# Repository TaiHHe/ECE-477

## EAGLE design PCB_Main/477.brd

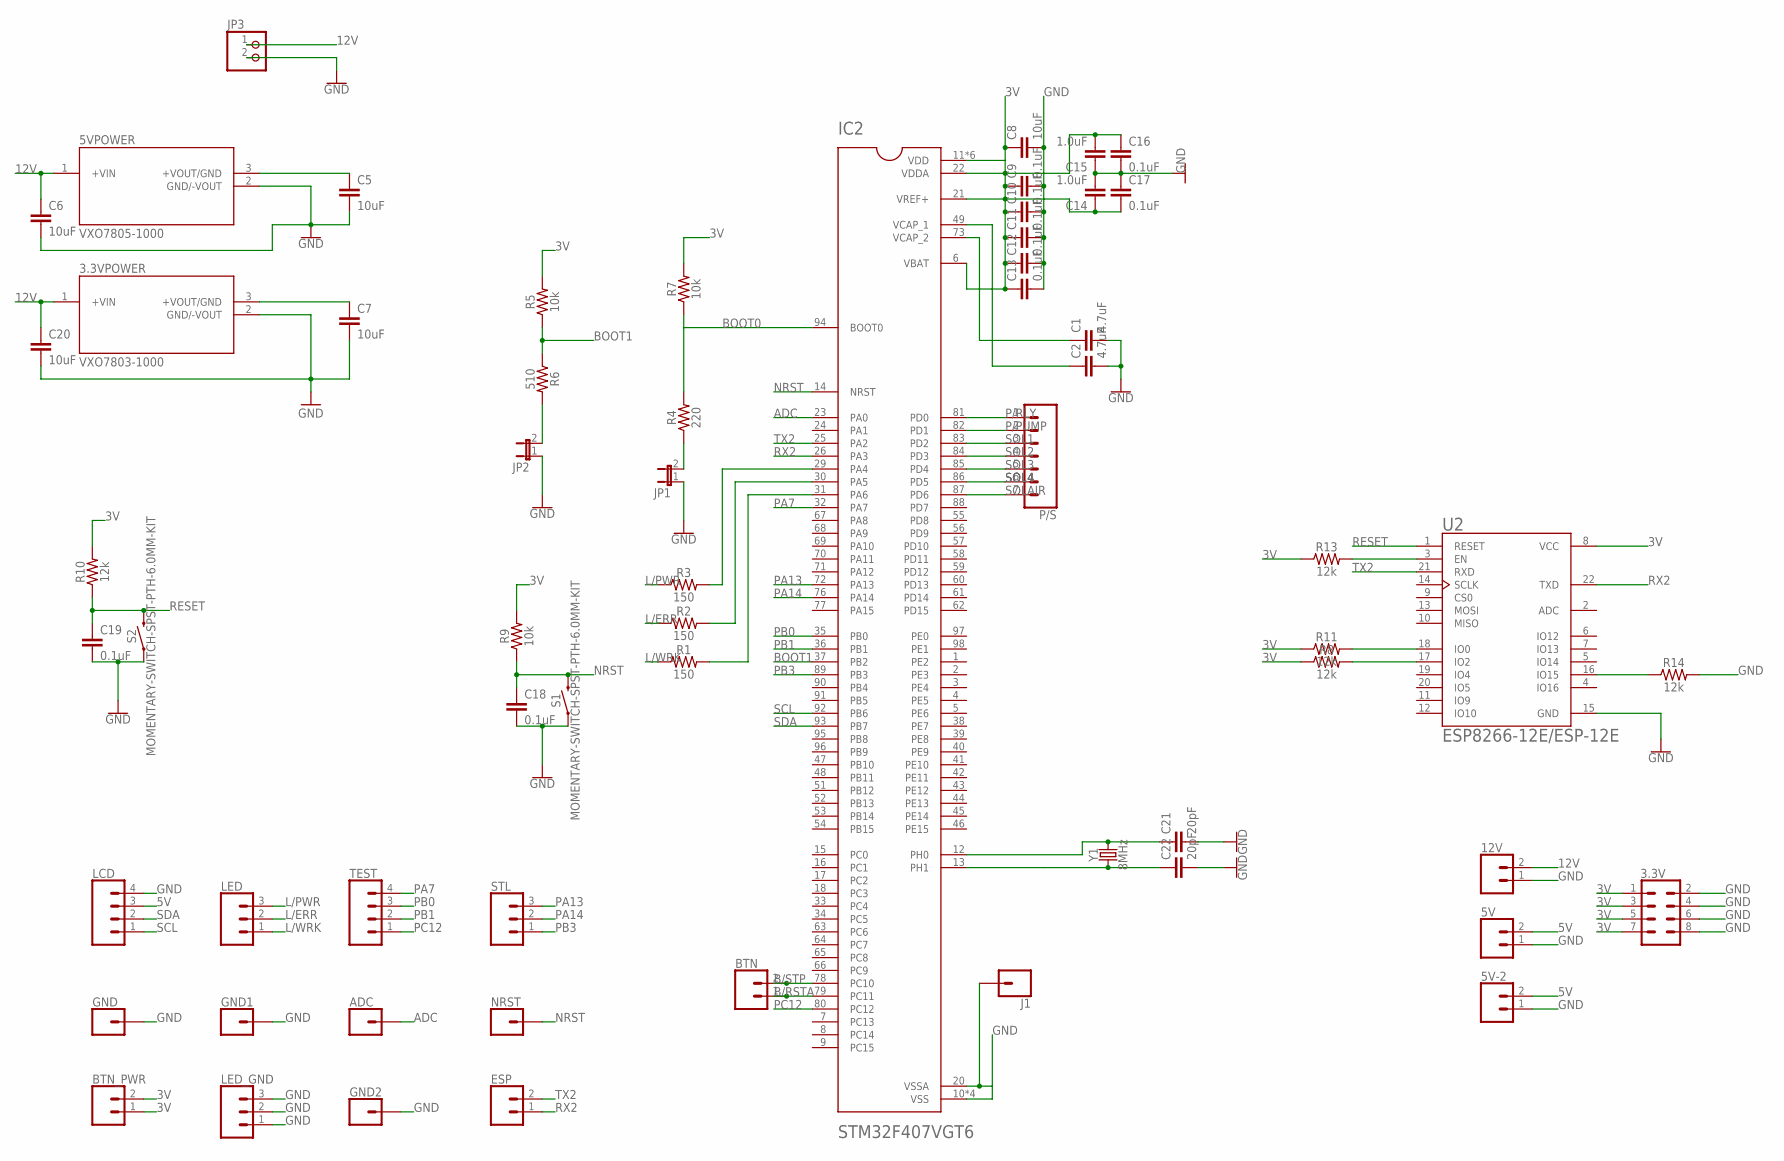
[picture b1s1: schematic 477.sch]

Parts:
3.3V: CONN_04X2; 2X4
3.3VPOWER: VXO7803-1000; CONV_VXO7803-1000
5V, 5V-2, 12V: CONN_02; 1X02
5VPOWER: VXO7805-1000; CONV_VXO7805-1000
ADC: CONN_01; 1X01
BTN: CONN_02; 1X02
BTN_PWR: CONN_02; 1X02
C1, C2: 4.7uF; 0603
C5, C6, C7, C8, C20: 10uF; 0603
C9, C10, C11, C12, C13, C16, C17, C18, C19: 0.1uF; 0402
C14, C15: 1.0uF; 0402
C21, C22: 20pF; 0603
ESP: CONN_02; 1X02
GND, GND1: CONN_01PTH_NO_SILK_YES_STOP; 1X01_NO_SILK
GND2: CONN_01; 1X01
IC2: STM32F407VGT6; QFP50P1600X1600X160-100N
J1: CONN_01PTH_NO_SILK_YES_STOP; 1X01_NO_SILK
JP1, JP2: JP1E; JP1
JP3: PINHD-1X2; 1X02
LCD: CONN_04; 1X04
LED: CONN_03; 1X03
LED_GND: CONN_03; 1X03
NRST: CONN_01; 1X01
P/S: CONN_07; 1X07
R1, R2, R3: 150; 0603
R4: 220; 0603
R5, R7, R9: 10k; 0603
R6: 510; 0603
R8, R10, R11, R13, R14: 12k; 0603
S1, S2: MOMENTARY-SWITCH-SPST-PTH-6.0MM-KIT; TACTILE_SWITCH_PTH_6.0MM_KIT
STL: CONN_03; 1X03
TEST: CONN_04; 1X04
U2: ESP8266-12E/ESP-12E; XCVR_ESP8266-12E/ESP-12E
Y1: 8MHz; HC49UP

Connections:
3V: 3.3V.1, 3.3V.3, 3.3V.5, 3.3V.7, 3.3VPOWER.3 (+VOUT/GND), BTN_PWR.1, BTN_PWR.2, C7.1, C8.1, C9.1, C10.1, C11.1, C12.1, C13.1, C14.1, C15.2, C16.1, C17.2, IC2.6 (VBAT), IC2.11 (VDD), IC2.19 (VDD), IC2.21 (VREF+), IC2.22 (VDDA), IC2.28 (VDD), IC2.50 (VDD), IC2.75 (VDD), IC2.100 (VDD), R5.2, R7.2, R8.1, R9.2, R10.2, R11.1, R13.1, U2.8 (VCC)
5V: 5V.2, 5V-2.2, 5VPOWER.3 (+VOUT/GND), C5.1, LCD.3
12V: 3.3VPOWER.1 (+VIN), 5VPOWER.1 (+VIN), 12V.2, C6.1, C20.1, JP3.1
ADC: ADC.1, IC2.23 (PA0)
B/RSTA: BTN.1, IC2.79 (PC11)
B/STP: BTN.2, IC2.78 (PC10)
BOOT0: IC2.94 (BOOT0), R4.2, R7.1
BOOT1: IC2.37 (PB2), R5.1, R6.1
EN: R13.2, U2.3 (EN)
GND: 3.3V.2, 3.3V.4, 3.3V.6, 3.3V.8, 3.3VPOWER.2 (GND/-VOUT), 5V.1, 5V-2.1, 5VPOWER.2 (GND/-VOUT), 12V.1, C1.2, C2.2, C5.2, C6.2, C7.2, C8.2, C9.2, C10.2, C11.2, C12.2, C13.2, C14.2, C15.1, C16.2, C17.1, C18.2, C19.2, C20.2, C21.2, C22.2, GND.1, GND1.1, GND2.1, IC2.10 (VSS), IC2.27 (VSS), IC2.74 (VSS), IC2.99 (VSS), JP1.1, JP2.1, JP3.2, LCD.4, LED_GND.1, LED_GND.2, LED_GND.3, R14.2, S1.1, S2.1, U2.15 (GND)
L/ERR: LED.2, R2.1
L/PWR: LED.3, R3.1
L/WRK: LED.1, R1.1
unnamed: IC2.29 (PA4), R3.2
unnamed: IC2.30 (PA5), R2.2
unnamed: C22.1, IC2.13 (PH1), Y1.1
unnamed: IC2.31 (PA6), R1.2
unnamed: R11.2, U2.18 (IO0)
unnamed: R8.2, U2.17 (IO2)
unnamed: R14.1, U2.16 (IO15)
unnamed: C21.1, IC2.12 (PH0), Y1.2
unnamed: C1.1, IC2.73 (VCAP_2)
unnamed: JP2.2, R6.2
unnamed: C2.1, IC2.49 (VCAP_1)
unnamed: IC2.20 (VSSA), J1.1
unnamed: JP1.2, R4.1
NRST: C18.1, IC2.14 (NRST), NRST.1, R9.1, S1.3 (2)
P/PUMP: IC2.82 (PD1), P/S.2
P/RLY: IC2.81 (PD0), P/S.1
PA7: IC2.32 (PA7), TEST.4
PA13: IC2.72 (PA13), STL.3
PA14: IC2.76 (PA14), STL.2
PB0: IC2.35 (PB0), TEST.3
PB1: IC2.36 (PB1), TEST.2
PB3: IC2.89 (PB3), STL.1
PC12: IC2.80 (PC12), TEST.1
RESET: C19.1, R10.1, S2.3 (2), U2.1 (RESET)
RX2: ESP.1, IC2.26 (PA3), U2.22 (TXD)
SCL: IC2.92 (PB6), LCD.1
SDA: IC2.93 (PB7), LCD.2
SOL1: IC2.83 (PD2), P/S.3
SOL2: IC2.84 (PD3), P/S.4
SOL3: IC2.85 (PD4), P/S.5
SOL4: IC2.86 (PD5), P/S.6
SOLAIR: IC2.87 (PD6), P/S.7
TX2: ESP.2, IC2.25 (PA2), U2.21 (RXD)

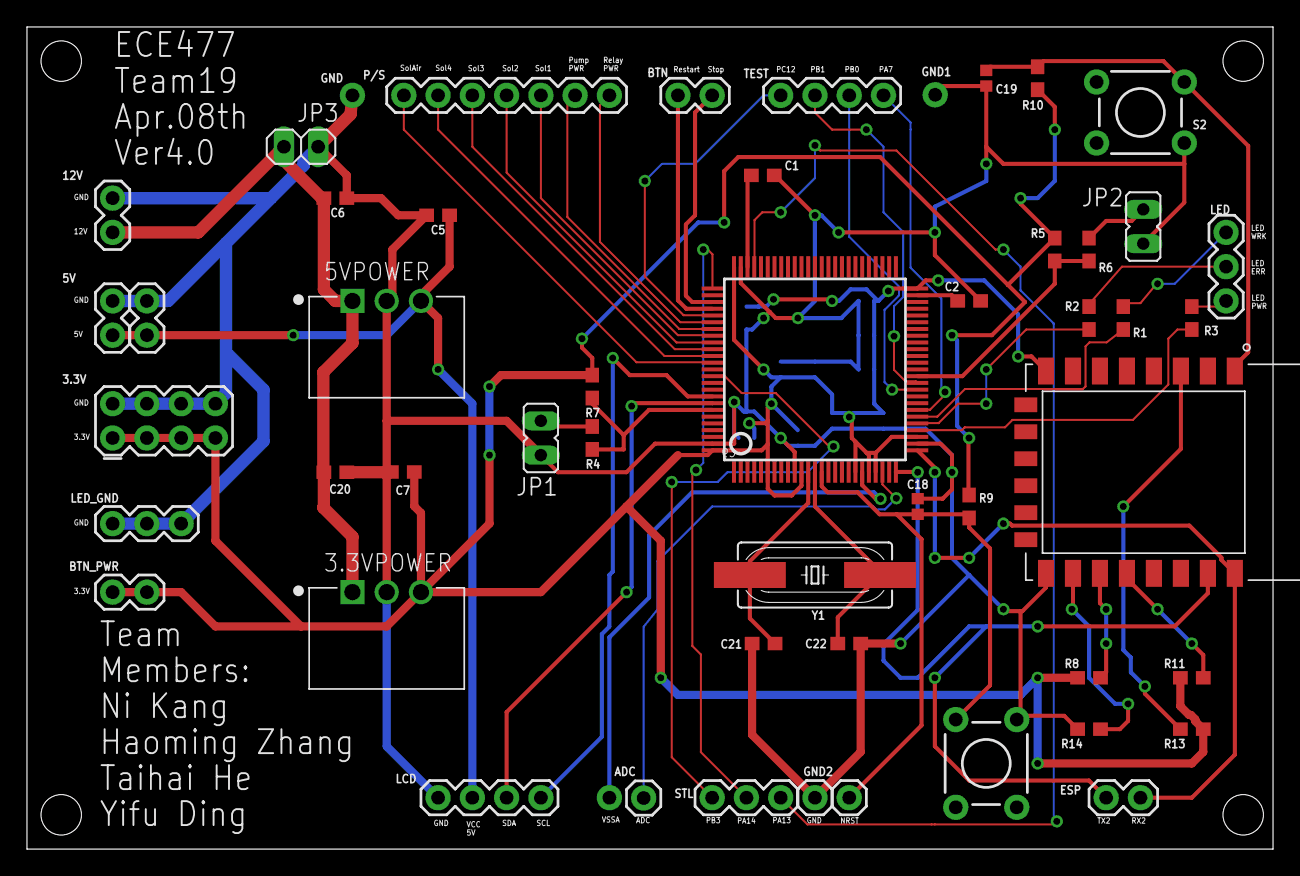
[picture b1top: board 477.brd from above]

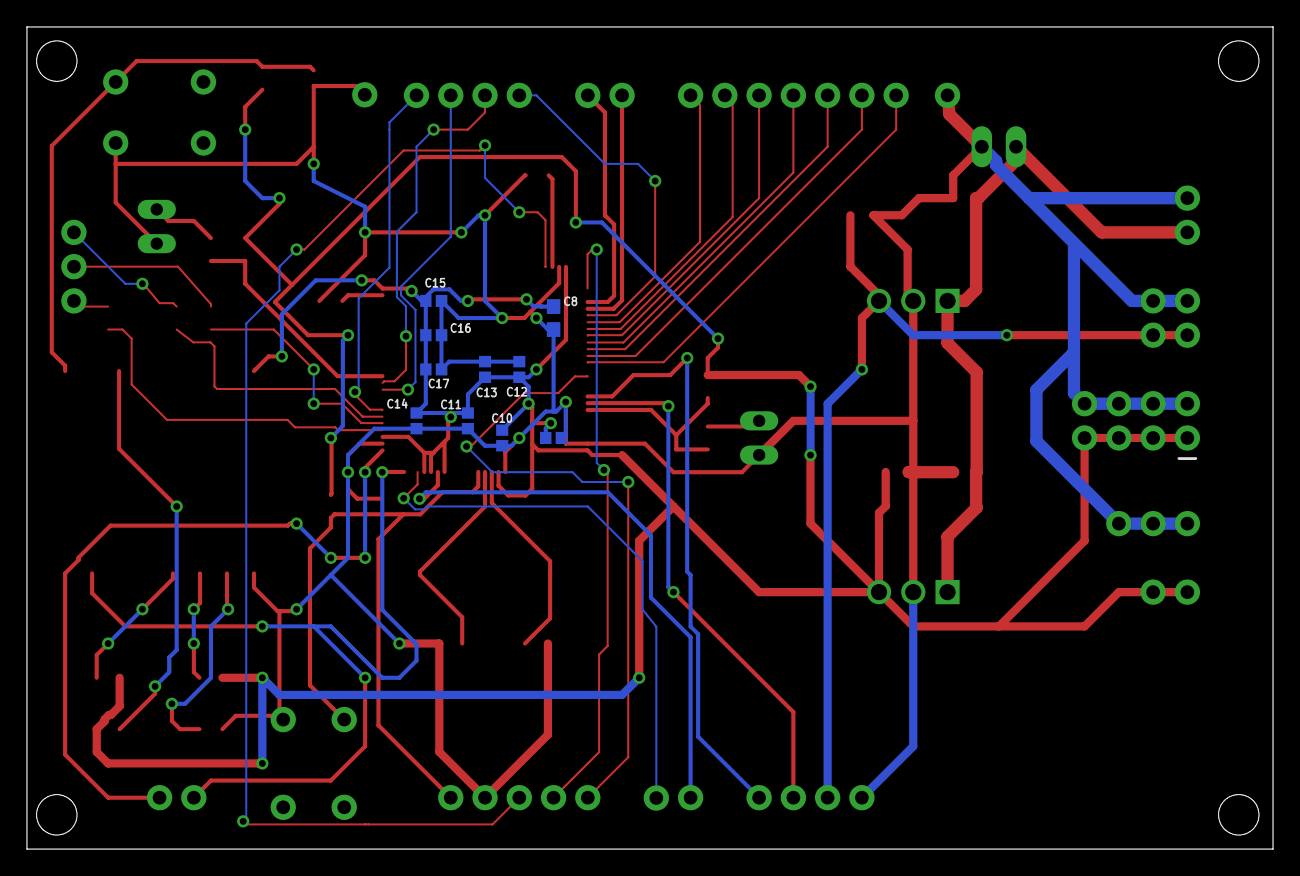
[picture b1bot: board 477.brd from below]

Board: 2 copper layers, 92.4 x 60.9 mm, 62 parts (10 on the bottom side), 46 nets.

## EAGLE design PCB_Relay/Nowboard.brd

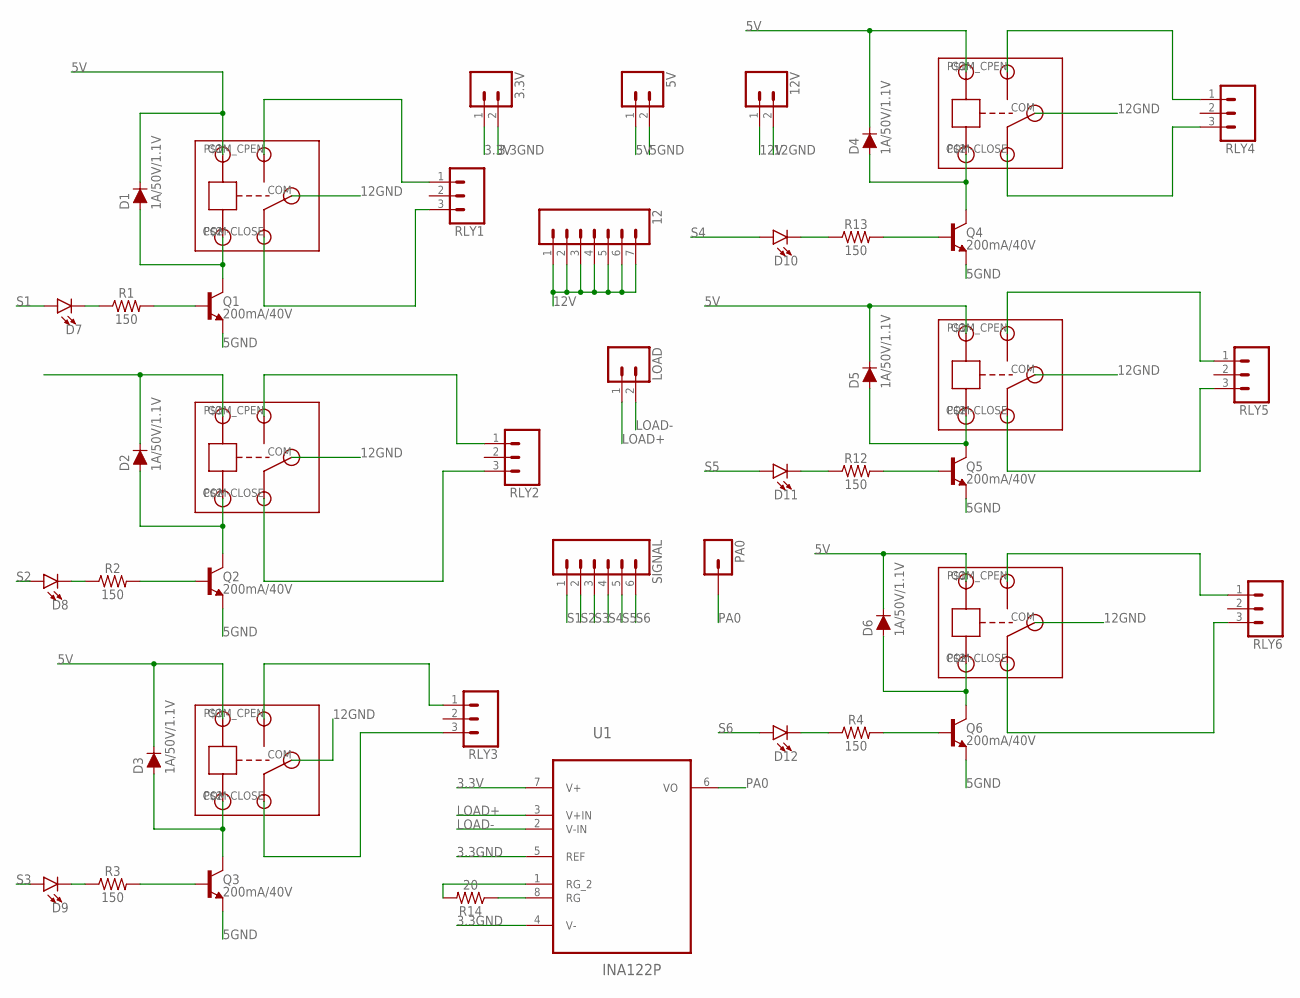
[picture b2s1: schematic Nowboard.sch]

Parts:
3.3V, 5V, 12V: CONN_02; 1X02
12: CONN_07; 1X07
D1, D2, D3, D4, D5, D6: 1A/50V/1.1V; DIODE-1N4001
D7, D8, D9, D10, D11, D12: LED3MM; LED_3MM
LOAD: CONN_02; 1X02
PA0: CONN_01; 1X01
Q1, Q2, Q3, Q4, Q5, Q6: 200mA/40V; TO-92
R1, R2, R3, R4, R12, R13: 150; 0603
R14: 20; 0603
RELAY1, RELAY2, RELAY3, RELAY4, RELAY5, RELAY6: RELAY
RLY1, RLY2, RLY3, RLY4, RLY5, RLY6: CONN_03; 1X03
SIGNAL: CONN_06NO_SILK_FEMALE_PTH; 1X06_NO_SILK
U1: INA122P; DIP254P762X508-8

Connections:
3.3GND: 3.3V.2, U1.4 (V-), U1.5 (REF)
3.3V: 3.3V.1, U1.7 (V+)
5GND: 5V.2, Q1.1 (E), Q2.1 (E), Q3.1 (E), Q4.1 (E), Q5.1 (E), Q6.1 (E)
5V: 5V.1, D1.C, D3.C, D4.C, D5.C, D6.C, RELAY1.P$1 (IN), RELAY3.P$1 (IN), RELAY4.P$1 (IN), RELAY5.P$1 (IN), RELAY6.P$1 (IN)
12GND: 12V.2, RELAY1.COM, RELAY2.COM, RELAY3.COM, RELAY4.COM, RELAY5.COM, RELAY6.COM
12V: 12.1, 12.2, 12.3, 12.4, 12.5, 12.6, 12.7, 12V.1
LOAD+: LOAD.1, U1.3 (V+IN)
LOAD-: LOAD.2, U1.2 (V-IN)
unnamed: D1.A, Q1.3 (C), RELAY1.P$2 (GND)
unnamed: R14.1, U1.8 (RG)
unnamed: RELAY3.COM-CLOSE, RLY3.3
unnamed: RELAY4.COM_CPEN (COM-OPEN), RLY4.1
unnamed: D2.A, Q2.3 (C), RELAY2.P$2 (GND)
unnamed: D3.A, Q3.3 (C), RELAY3.P$2 (GND)
unnamed: D6.A, Q6.3 (C), RELAY6.P$2 (GND)
unnamed: D5.A, Q5.3 (C), RELAY5.P$2 (GND)
unnamed: D4.A, Q4.3 (C), RELAY4.P$2 (GND)
unnamed: Q4.2 (B), R13.2
unnamed: Q5.2 (B), R12.2
unnamed: Q6.2 (B), R4.2
unnamed: D12.K (C), R4.1
unnamed: D11.K (C), R12.1
unnamed: D10.K (C), R13.1
unnamed: Q3.2 (B), R3.2
unnamed: D9.K (C), R3.1
unnamed: D8.K (C), R2.1
unnamed: Q2.2 (B), R2.2
unnamed: D7.K (C), R1.1
unnamed: Q1.2 (B), R1.2
unnamed: RELAY1.COM-CLOSE, RLY1.3
unnamed: RELAY1.COM_CPEN (COM-OPEN), RLY1.1
unnamed: RELAY2.COM-CLOSE, RLY2.3
unnamed: D2.C, RELAY2.P$1 (IN)
unnamed: RELAY4.COM-CLOSE, RLY4.3
unnamed: RELAY3.COM_CPEN (COM-OPEN), RLY3.1
unnamed: RELAY2.COM_CPEN (COM-OPEN), RLY2.1
unnamed: RELAY6.COM-CLOSE, RLY6.3
unnamed: RELAY6.COM_CPEN (COM-OPEN), RLY6.1
unnamed: RELAY5.COM-CLOSE, RLY5.3
unnamed: RELAY5.COM_CPEN (COM-OPEN), RLY5.1
unnamed: R14.2, U1.1 (RG_2)
PA0: PA0.1, U1.6 (VO)
S1: D7.A, SIGNAL.1
S2: D8.A, SIGNAL.2
S3: D9.A, SIGNAL.3
S4: D10.A, SIGNAL.4
S5: D11.A, SIGNAL.5
S6: D12.A, SIGNAL.6

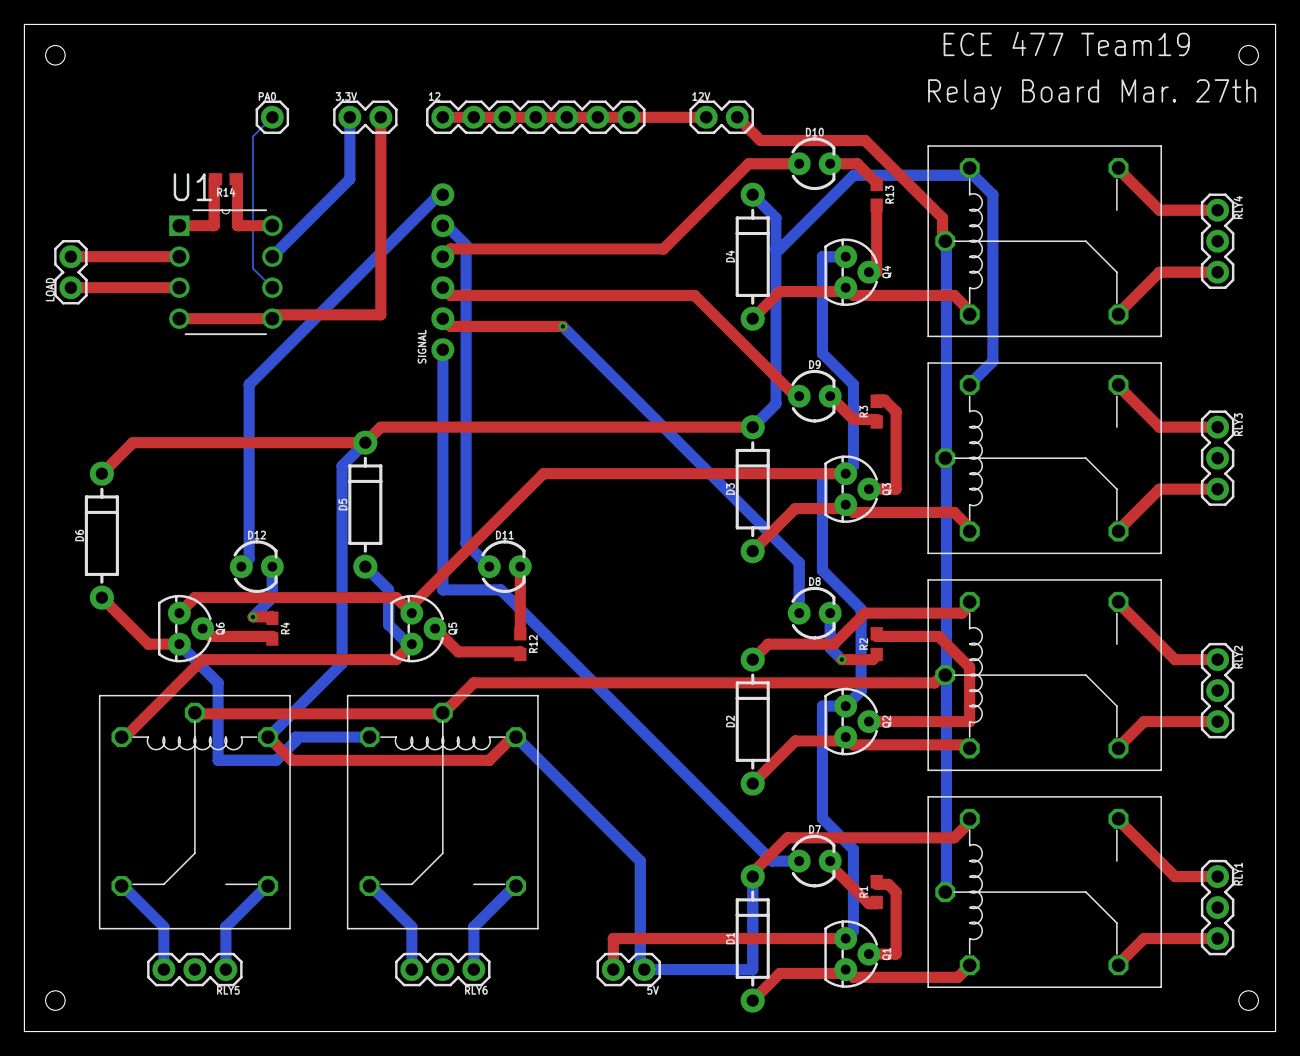
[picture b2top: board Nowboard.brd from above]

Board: 2 copper layers, 102.5 x 82.5 mm, 45 parts (0 on the bottom side), 48 nets.

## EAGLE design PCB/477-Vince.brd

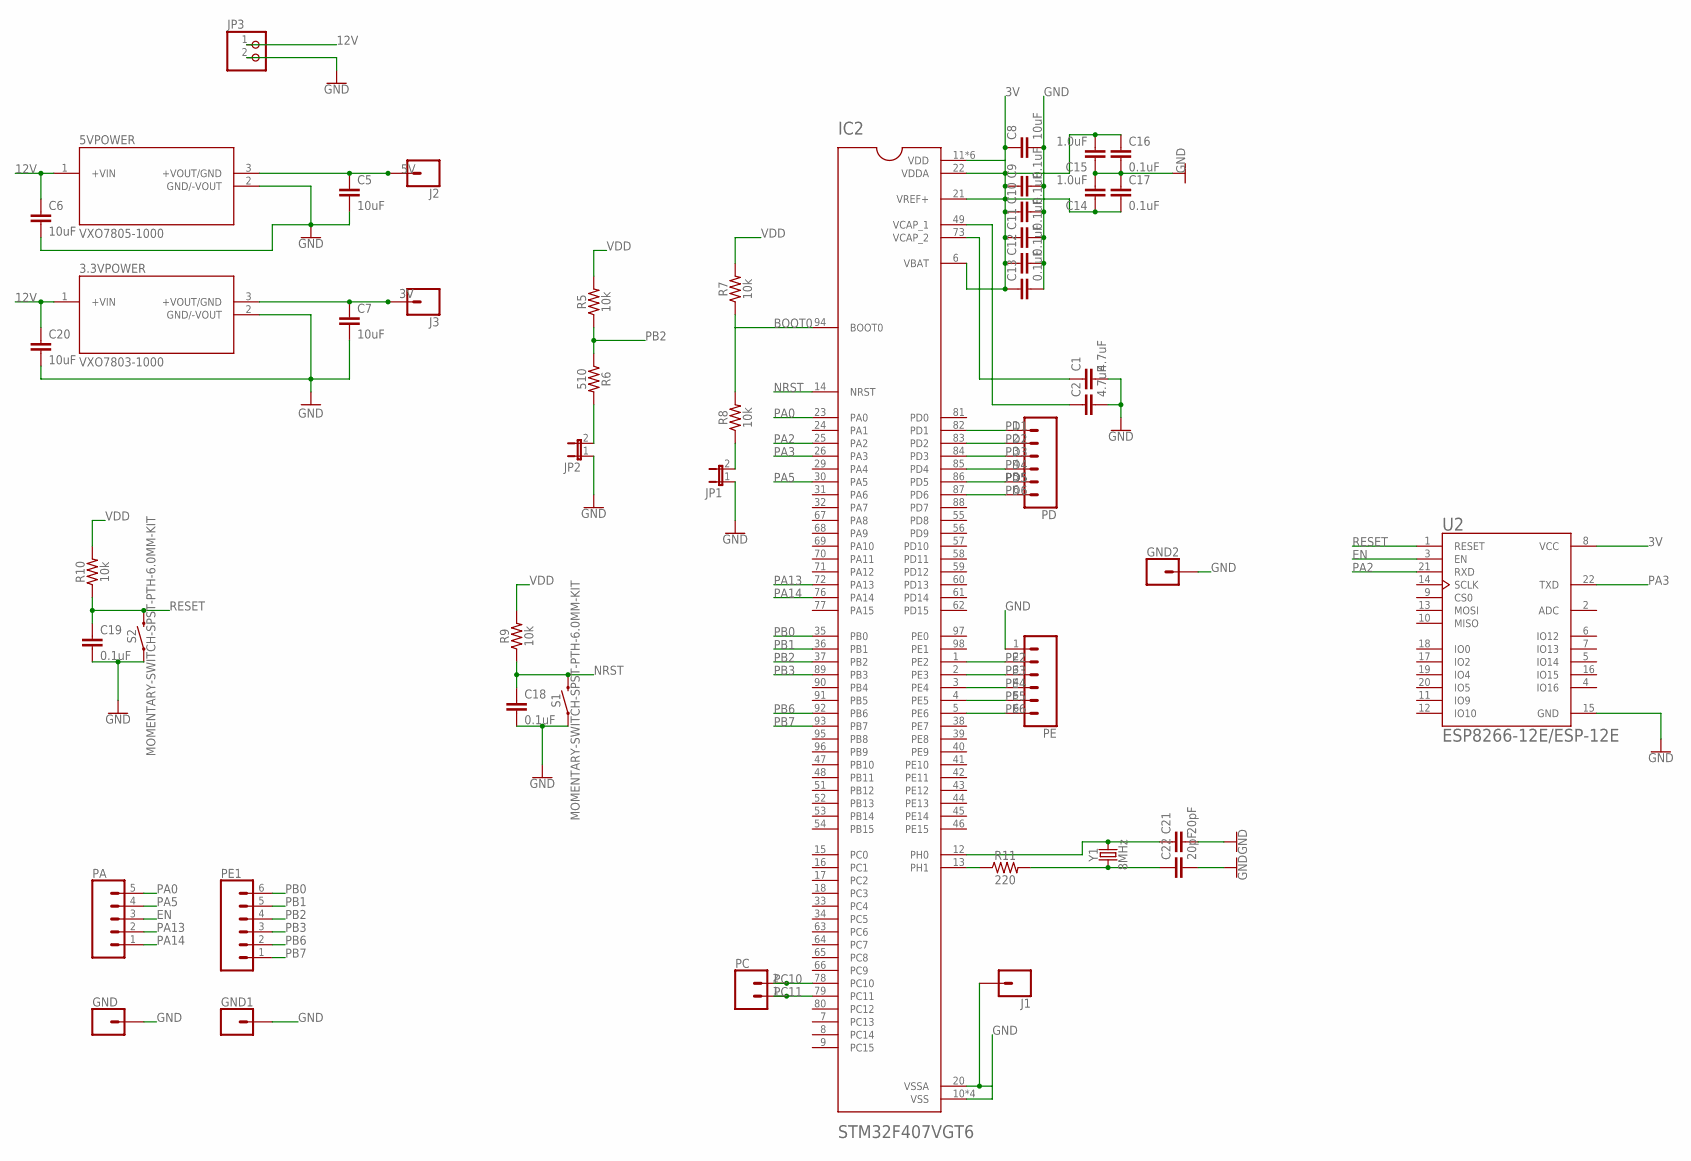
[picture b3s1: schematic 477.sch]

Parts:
3.3VPOWER: VXO7803-1000; CONV_VXO7803-1000
5VPOWER: VXO7805-1000; CONV_VXO7805-1000
C1, C2: 4.7uF; 0603
C5, C6, C7, C8, C20: 10uF; 0603
C9, C10, C11, C12, C13, C16, C17, C18, C19: 0.1uF; 0402
C14, C15: 1.0uF; 0402
C21, C22: 20pF; 0603
GND, GND1, GND2: CONN_01PTH_NO_SILK_YES_STOP; 1X01_NO_SILK
IC2: STM32F407VGT6; QFP50P1600X1600X160-100N
J1, J2, J3: CONN_01PTH_NO_SILK_YES_STOP; 1X01_NO_SILK
JP1, JP2: JP1E; JP1
JP3: PINHD-1X2; 1X02
PA: CONN_05; 1X05
PC: CONN_02; 1X02
PD: CONN_06NO_SILK_FEMALE_PTH; 1X06_NO_SILK
PE, PE1: CONN_06NO_SILK_FEMALE_PTH; 1X06_NO_SILK
R5, R7, R8, R9, R10: 10k; 0603
R6: 510; 0603
R11: 220; 0603
S1, S2: MOMENTARY-SWITCH-SPST-PTH-6.0MM-KIT; TACTILE_SWITCH_PTH_6.0MM_KIT
U2: ESP8266-12E/ESP-12E; XCVR_ESP8266-12E/ESP-12E
Y1: 8MHz; HC49UP

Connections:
3V: 3.3VPOWER.3 (+VOUT/GND), C7.1, C8.1, C9.1, C10.1, C11.1, C12.1, C13.1, C14.1, C15.2, C16.1, C17.2, IC2.6 (VBAT), IC2.11 (VDD), IC2.19 (VDD), IC2.21 (VREF+), IC2.22 (VDDA), IC2.28 (VDD), IC2.50 (VDD), IC2.75 (VDD), IC2.100 (VDD), J3.1, U2.8 (VCC)
5V: 5VPOWER.3 (+VOUT/GND), C5.1, J2.1
12V: 3.3VPOWER.1 (+VIN), 5VPOWER.1 (+VIN), C6.1, C20.1, JP3.1
BOOT0: IC2.94 (BOOT0), R7.1, R8.2
EN: PA.3, U2.3 (EN)
GND: 3.3VPOWER.2 (GND/-VOUT), 5VPOWER.2 (GND/-VOUT), C1.2, C2.2, C5.2, C6.2, C7.2, C8.2, C9.2, C10.2, C11.2, C12.2, C13.2, C14.2, C15.1, C16.2, C17.1, C18.2, C19.2, C20.2, C21.2, C22.2, GND.1, GND1.1, GND2.1, IC2.10 (VSS), IC2.27 (VSS), IC2.74 (VSS), IC2.99 (VSS), JP1.1, JP2.1, JP3.2, PE.1, S1.1, S2.1, U2.15 (GND)
unnamed: IC2.13 (PH1), R11.1
unnamed: C21.1, IC2.12 (PH0), Y1.2
unnamed: C22.1, R11.2, Y1.1
unnamed: C1.1, IC2.73 (VCAP_2)
unnamed: JP2.2, R6.2
unnamed: C2.1, IC2.49 (VCAP_1)
unnamed: IC2.20 (VSSA), J1.1
unnamed: JP1.2, R8.1
NRST: C18.1, IC2.14 (NRST), R9.1, S1.3 (2)
PA0: IC2.23 (PA0), PA.5
PA2: IC2.25 (PA2), U2.21 (RXD)
PA3: IC2.26 (PA3), U2.22 (TXD)
PA5: IC2.30 (PA5), PA.4
PA13: IC2.72 (PA13), PA.2
PA14: IC2.76 (PA14), PA.1
PB0: IC2.35 (PB0), PE1.6
PB1: IC2.36 (PB1), PE1.5
PB2: IC2.37 (PB2), PE1.4, R5.1, R6.1
PB3: IC2.89 (PB3), PE1.3
PB6: IC2.92 (PB6), PE1.2
PB7: IC2.93 (PB7), PE1.1
PC10: IC2.78 (PC10), PC.2
PC11: IC2.79 (PC11), PC.1
PD1: IC2.82 (PD1), PD.1
PD2: IC2.83 (PD2), PD.2
PD3: IC2.84 (PD3), PD.3
PD4: IC2.85 (PD4), PD.4
PD5: IC2.86 (PD5), PD.5
PD6: IC2.87 (PD6), PD.6
PE2: IC2.1 (PE2), PE.2
PE3: IC2.2 (PE3), PE.3
PE4: IC2.3 (PE4), PE.4
PE5: IC2.4 (PE5), PE.5
PE6: IC2.5 (PE6), PE.6
RESET: C19.1, R10.1, S2.3 (2), U2.1 (RESET)
VDD: R5.2, R7.2, R9.2, R10.2

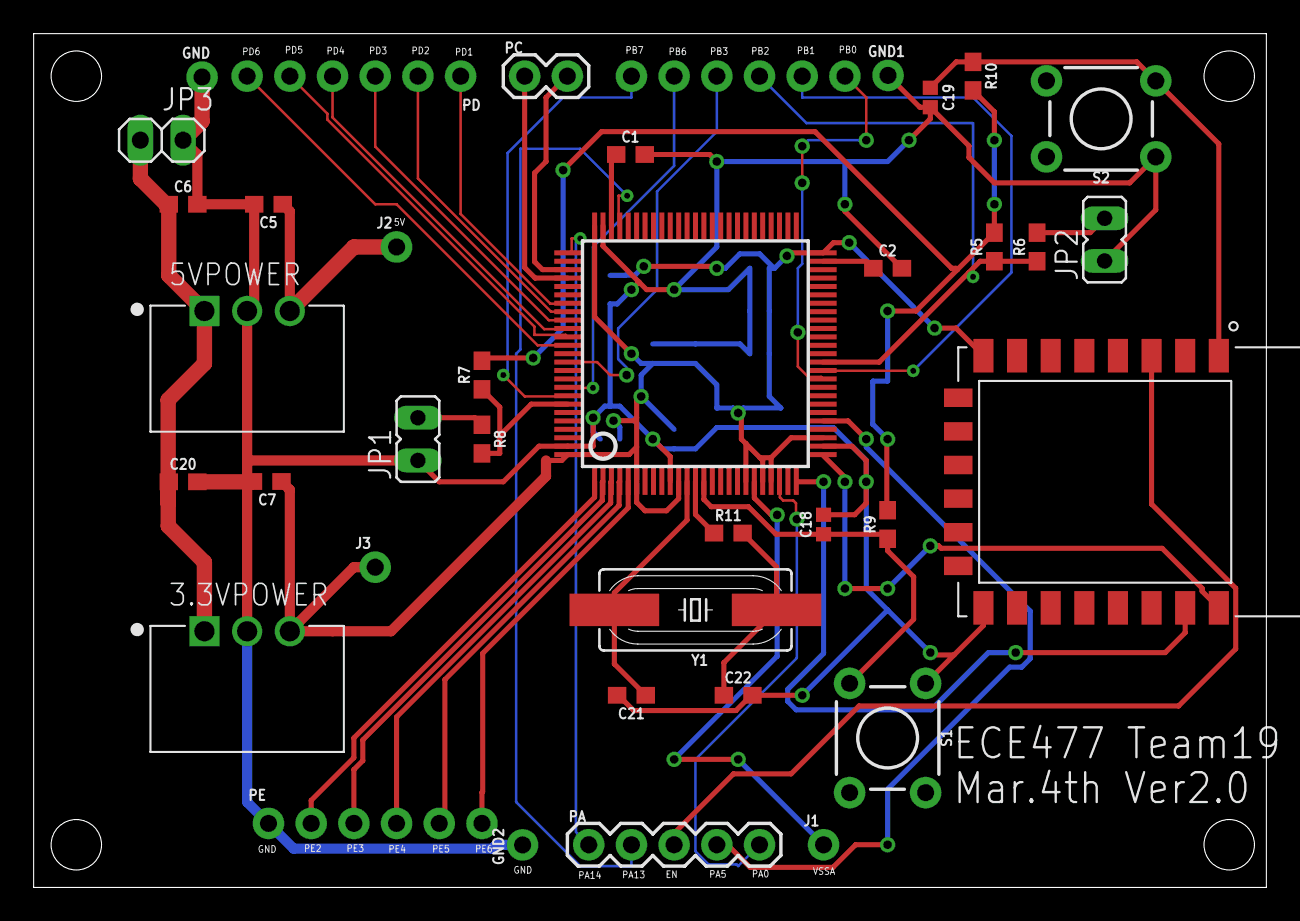
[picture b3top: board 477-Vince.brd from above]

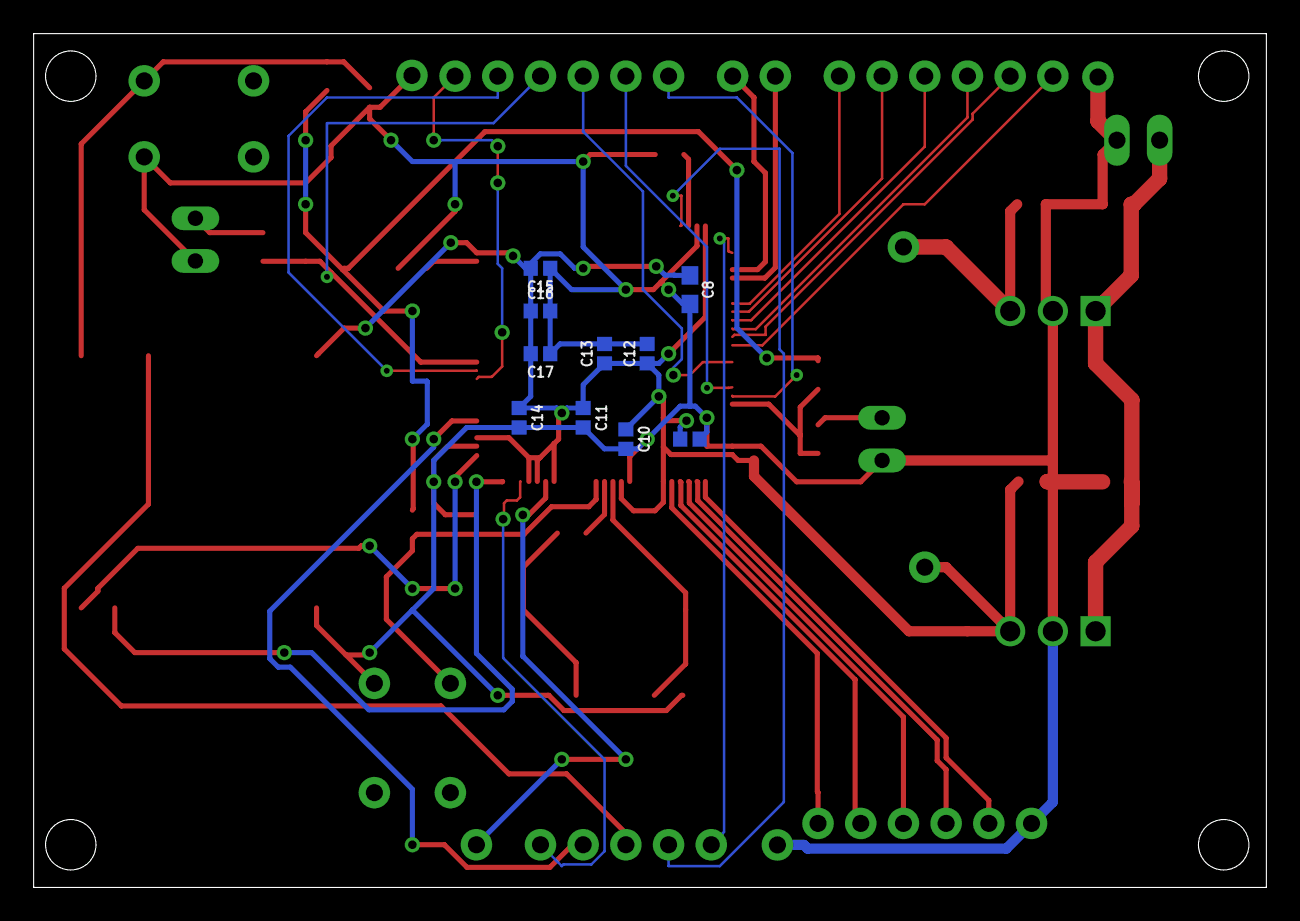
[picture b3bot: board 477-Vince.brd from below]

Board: 2 copper layers, 73.3 x 50.8 mm, 48 parts (10 on the bottom side), 42 nets.

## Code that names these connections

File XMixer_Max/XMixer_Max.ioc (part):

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Mcu.Name=STM32F407V(E-G)Tx
Mcu.Package=LQFP100
Mcu.UserName=STM32F407VGTx
PA0-WKUP.Signal=ADCx_IN0
PA2.Mode=Asynchronous
PA2.Signal=USART2_TX
PA3.Mode=Asynchronous
PA3.Signal=USART2_RX
PA4.GPIOParameters=GPIO_Label
PA4.GPIO_Label=LED_Power
PA4.Signal=GPIO_Output
PA5.GPIOParameters=GPIO_Label
PA5.GPIO_Label=LED_Error
PA5.Signal=GPIO_Output
PA6.GPIOParameters=GPIO_Label
PA6.GPIO_Label=LED_Working
PA6.Signal=GPIO_Output
PA7.Signal=GPIO_Output
PB0.Signal=GPIO_Output
PB1.Signal=GPIO_Output
PB10.Mode=Asynchronous
PB10.Signal=USART3_TX
PB11.Mode=Asynchronous
PB11.Signal=USART3_RX
PB2.GPIOParameters=GPIO_Label
PB2.GPIO_Label=Boot1
PB2.Signal=GPIO_Output
PB6.Mode=I2C
PB6.Signal=I2C1_SCL
PB7.Mode=I2C
PB7.Signal=I2C1_SDA
PC10.GPIOParameters=GPIO_Label
PC10.GPIO_Label=Button_Stop
PC10.Signal=GPIO_Input
PC11.GPIOParameters=GPIO_Label
PC11.GPIO_Label=Button_Restart
PC11.Signal=GPIO_Input
PC12.Signal=GPIO_Input
PD0.GPIOParameters=GPIO_Label
PD0.GPIO_Label=Relay_Power
PD0.Signal=GPIO_Output
PD1.GPIOParameters=GPIO_Label
PD1.GPIO_Label=Pump_Power
PD1.Signal=GPIO_Output
PD2.GPIOParameters=GPIO_Label
PD2.GPIO_Label=Solenoid_1
PD2.Signal=GPIO_Output
PD3.GPIOParameters=GPIO_Label
PD3.GPIO_Label=Solenoid_2
PD3.Signal=GPIO_Output
PD4.GPIOParameters=GPIO_Label
PD4.GPIO_Label=Solenoid_3
PD4.Signal=GPIO_Output
PD5.GPIOParameters=GPIO_Label
PD5.GPIO_Label=Solenoid_4
PD5.Signal=GPIO_Output
PD6.GPIOParameters=GPIO_Label
PD6.GPIO_Label=Solenoid_Air
PD6.Signal=GPIO_Output
PH0-OSC_IN.Mode=HSE-External-Oscillator
PH0-OSC_IN.Signal=RCC_OSC_IN
PH1-OSC_OUT.Mode=HSE-External-Oscillator
PH1-OSC_OUT.Signal=RCC_OSC_OUT
RCC.HSE_VALUE=8000000
RCC.SYSCLKFreq_VALUE=16000000
board=custom

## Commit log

2019-02-10 Sever + esp8266 connection, initial version
2019-02-13 Updated to connect lab router
2019-02-14 Update some sever settings
2019-02-15 Finished sever to esp8266 communication.
2019-02-15 Finalized
2019-02-15 Finished communication between esp8266 and stm32
2019-02-15 Added Test_UART project
2019-02-20 Updated server appearance and Updated internal logic
2019-03-16 Finished the basic sturcture of MCU program.
2019-03-18 ECE-477
    Added PCB files
2019-03-19 Added ADC related logic and modified status checking logic.
2019-03-20 update server and socket code
2019-03-24 update esp8266 settings & server socket listening algorithm
2019-03-24 update to local version
2019-03-27 Changed foldername
2019-03-27 Added ADC logic and modified mixing logic and GPIO usage. Need to add stop logic.
2019-03-30 Minor update
2019-03-30 Seperate socket connection from server side
2019-03-30 Updated the logic for esp8266 and add shebang line for flask and socket
2019-03-30 Change file mod for connect and app, converted dos file to unix file format
2019-03-30 Established communication between flask and esp
2019-03-31 Added server file watchdog
2019-03-31 Update watchdog
2019-03-31 updared
2019-03-31 updated watchdog algorithm
2019-03-31 Changed file mode
2019-03-31 Finished
2019-04-01 Updated PCB files
    Modified main PCB and added the second PCB for relay
2019-04-04 Finished Software Side of Senior Design
2019-04-07 Changed esp8266 connection
2019-04-29 Project Finished

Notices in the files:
parts and their libraries:
SparkFun-Capacitors: Licensing: Creative Commons ShareAlike 4.0 International - https://creativecommons.org/licenses/by-sa/4.0
